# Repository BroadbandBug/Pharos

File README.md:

Pharos
======

APRS MSP430 Beacon

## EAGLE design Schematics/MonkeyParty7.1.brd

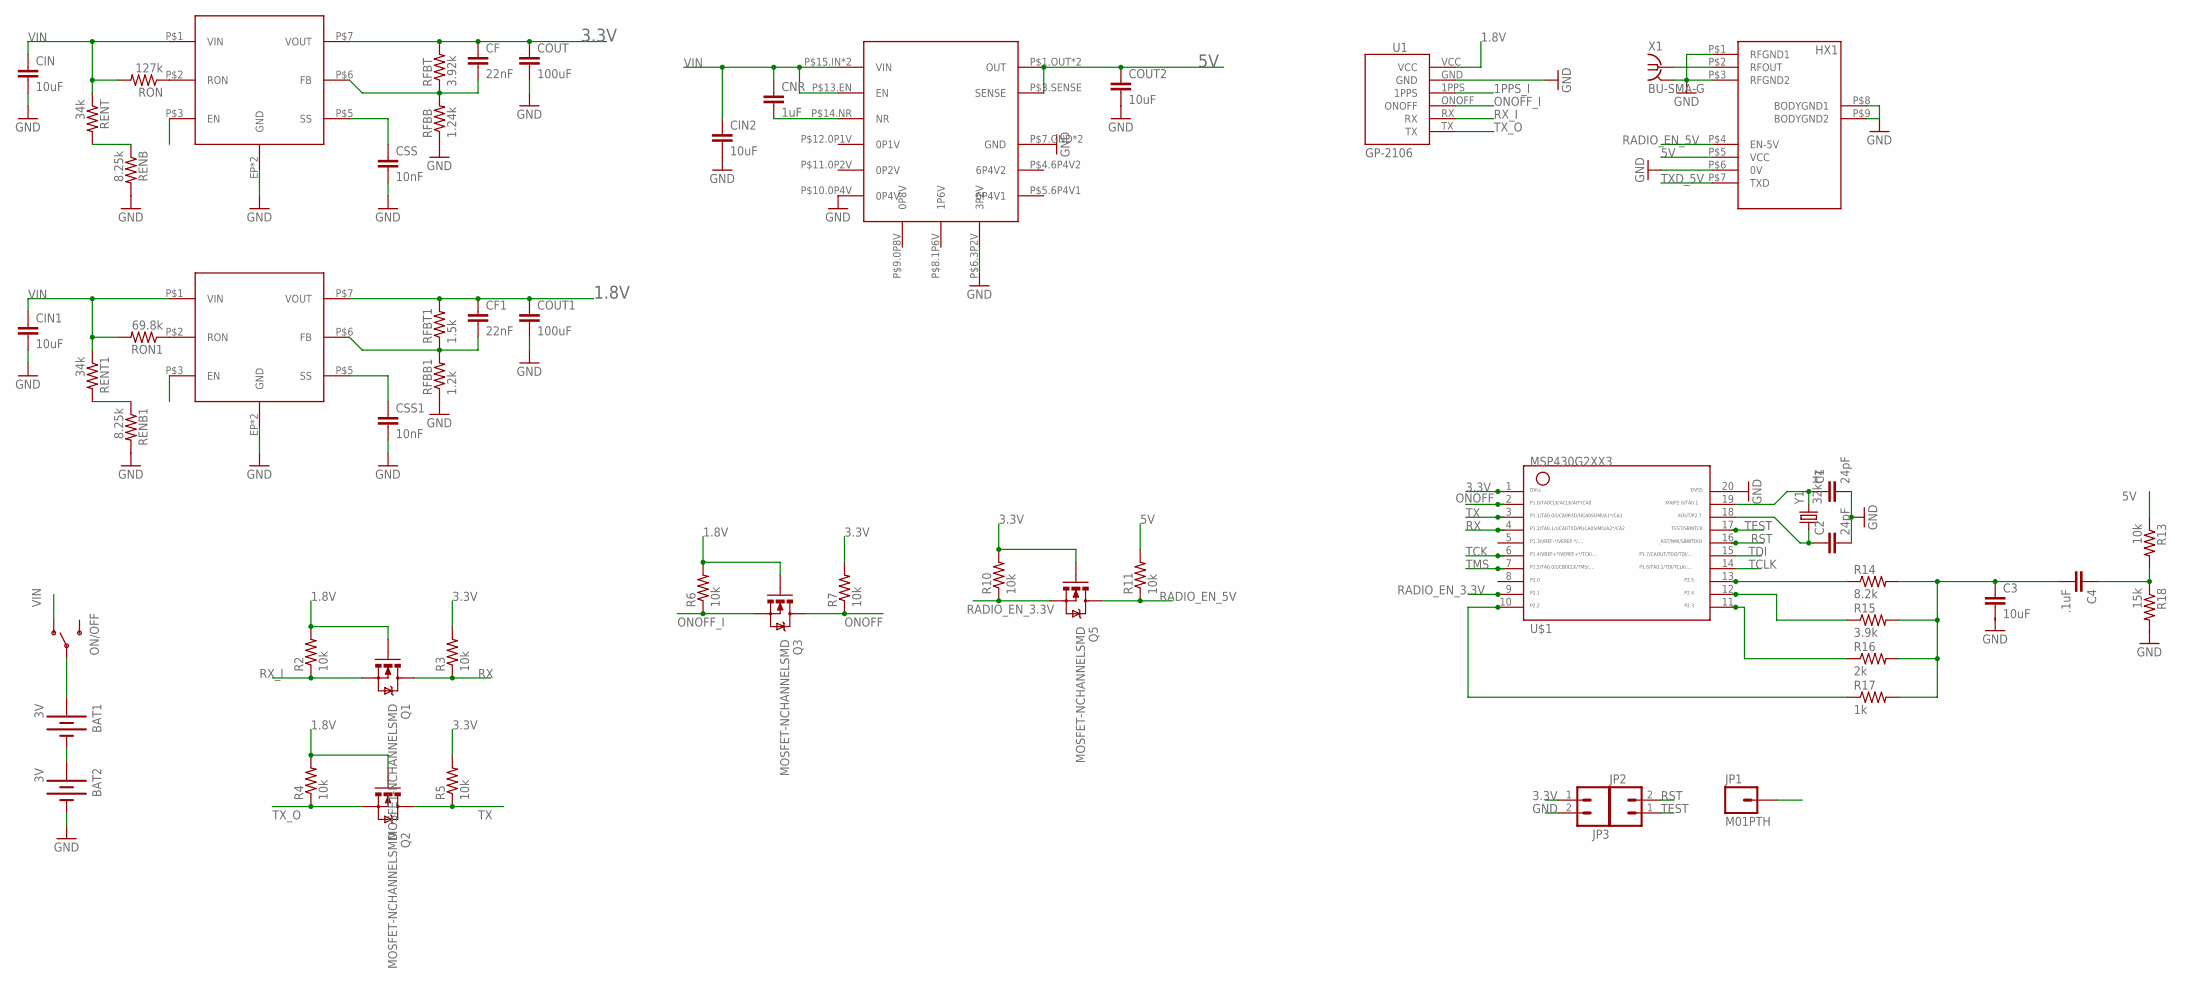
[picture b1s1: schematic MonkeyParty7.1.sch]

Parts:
1.8VREG, 3.3VREG: LMZ12001; TO-PMOD7PIN
5VREG: TPS7A4700; S-PVQFN-N20
BAT1, BAT2: 3V; BATTCON_245MM
C1, C2: 24pF; 1210
C3: 10uF; 0805
C4: .1uF; 0805
CF, CF1: 22nF; 0805
CIN, CIN1, CIN2: 10uF; 0805
CNR: 1uF; 0805
COUT, COUT1: 100uF; 1210
COUT2: 10uF; 0805
CSS, CSS1: 10nF; 1210
JP1: M01PTH; 1X01
JP2, JP3: M02PTH; 1X02
ON/OFF: SWITCH-SPSTKIT; SWITCH-SPDT_KIT
Q1, Q2, Q3, Q5: MOSFET-NCHANNELSMD; SOT23-3
R2, R3, R4, R5, R6, R7, R10, R11, R13: 10k; 0805
R14: 8.2k; 0805
R15: 3.9k; 0805
R16: 2k; 0805
R17: 1k; 0805
R18: 15k; 0805
RENB, RENB1: 8.25k; 0805
RENT, RENT1: 34k; 0805
RFBB: 1.24k; 0805
RFBB1: 1.2k; 0805
RFBT: 3.92k; 0805
RFBT1: 1.5k; 0805
RON: 127k; 0805
RON1: 69.8k; 0805
U1: GP-2106
U$1: G2XX3---PW20; PW20
U$2: HX1
X1: BU-SMA-G
Y1: 32kHz; CRYSTAL-32KHZ-SMD

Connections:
1.8V: 1.8VREG.P$7 (VOUT), CF1.1, COUT1.1, Q1.1 (G), Q2.1 (G), Q3.1 (G), R2.2, R4.2, R6.2, RFBT1.2, U1.VCC
1PPS_I: U1.1PPS
3.3V: 3.3VREG.P$7 (VOUT), CF.1, COUT.1, JP3.1, Q5.1 (G), R3.2, R5.2, R7.2, R10.2, RFBT.2, U$1.1
5V: 5VREG.P$1.OUT (OUT), 5VREG.P$3.SENSE (SENSE), 5VREG.P$20.OUT (OUT), COUT2.1, R11.2, R13.1, U$2.P$5 (VCC)
GND: 1.8VREG.EP (GND), 1.8VREG.P$4 (GND), 3.3VREG.EP (GND), 3.3VREG.P$4 (GND), 5VREG.P$6.3P2V (3P2V), 5VREG.P$7.GND (GND), 5VREG.P$10.0P4V (0P4V), 5VREG.P$21.GND (GND), BAT2.2 (-), C1.2, C2.2, CIN.2, CIN1.2, CIN2.2, COUT.2, COUT1.2, COUT2.2, CSS.2, CSS1.2, JP3.2, RENB.2, RENB1.2, RFBB.1, RFBB1.1, U1.GND, U$1.20, U$2.P$1 (RFGND1), U$2.P$3 (RFGND2), U$2.P$6 (0V), U$2.P$8 (BODYGND1), U$2.P$9 (BODYGND2), X1.2, X1.3 (2), X1.4 (2), X1.5 (2)
unnamed: 3.3VREG.P$2 (RON), RON.1
unnamed: U$2.P$2 (RFOUT), X1.1
unnamed: RENB.1, RENT.2
unnamed: BAT1.2 (-), BAT2.1 (+)
unnamed: 3.3VREG.P$5 (SS), CSS.1
unnamed: 3.3VREG.P$6 (FB), CF.2, RFBB.2, RFBT.1
unnamed: 1.8VREG.P$2 (RON), RON1.1
unnamed: BAT1.1 (+), ON/OFF.2
unnamed: RENB1.1, RENT1.2
unnamed: 1.8VREG.P$5 (SS), CSS1.1
unnamed: 1.8VREG.P$6 (FB), CF1.2, RFBB1.2, RFBT1.1
unnamed: 5VREG.P$14.NR (NR), CNR.2
unnamed: C1.1, U$1.19, Y1.X2 (2)
unnamed: C2.1, U$1.18, Y1.X1 (1)
unnamed: R14.1, U$1.13
unnamed: R15.1, U$1.12
unnamed: R16.1, U$1.11
unnamed: R17.1, U$1.10
ONOFF: Q3.3 (D), R7.1, U$1.2
ONOFF_I: Q3.2 (S), R6.1, U1.ONOFF
RADIO_EN_3.3V: Q5.2 (S), R10.1, U$1.9
RADIO_EN_5V: Q5.3 (D), R11.1, U$2.P$4 (EN-5V)
RST: JP2.2, U$1.16
RX: Q1.3 (D), R3.1, U$1.4
RX_I: Q1.2 (S), R2.1, U1.RX
TCK: U$1.6
TCLK: U$1.14
TDI: U$1.15
TEST: JP2.1, U$1.17
TMS: U$1.7
TX: Q2.3 (D), R5.1, U$1.3
TXD_3.3V: C3.1, C4.2, R14.2, R15.2, R16.2, R17.2
TXD_5V: C4.1, R13.2, R18.1, U$2.P$7 (TXD)
TX_O: Q2.2 (S), R4.1, U1.TX
VIN: 1.8VREG.P$1 (VIN), 1.8VREG.P$3 (EN), 3.3VREG.P$1 (VIN), 3.3VREG.P$3 (EN), 5VREG.P$13.EN (EN), 5VREG.P$15.IN (VIN), 5VREG.P$16.IN (VIN), CIN.1, CIN1.1, CIN2.1, CNR.1, JP1.1, ON/OFF.1 (O), RENT.1, RENT1.1, RON.2, RON1.2

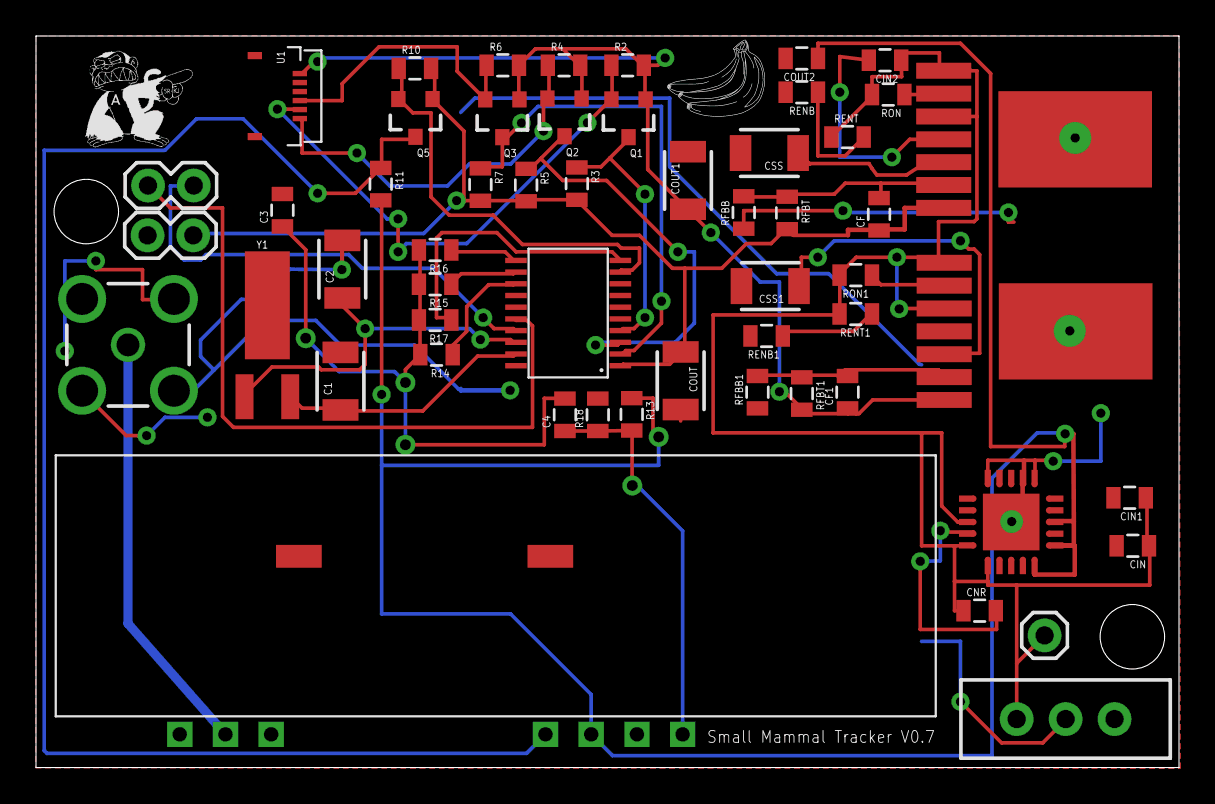
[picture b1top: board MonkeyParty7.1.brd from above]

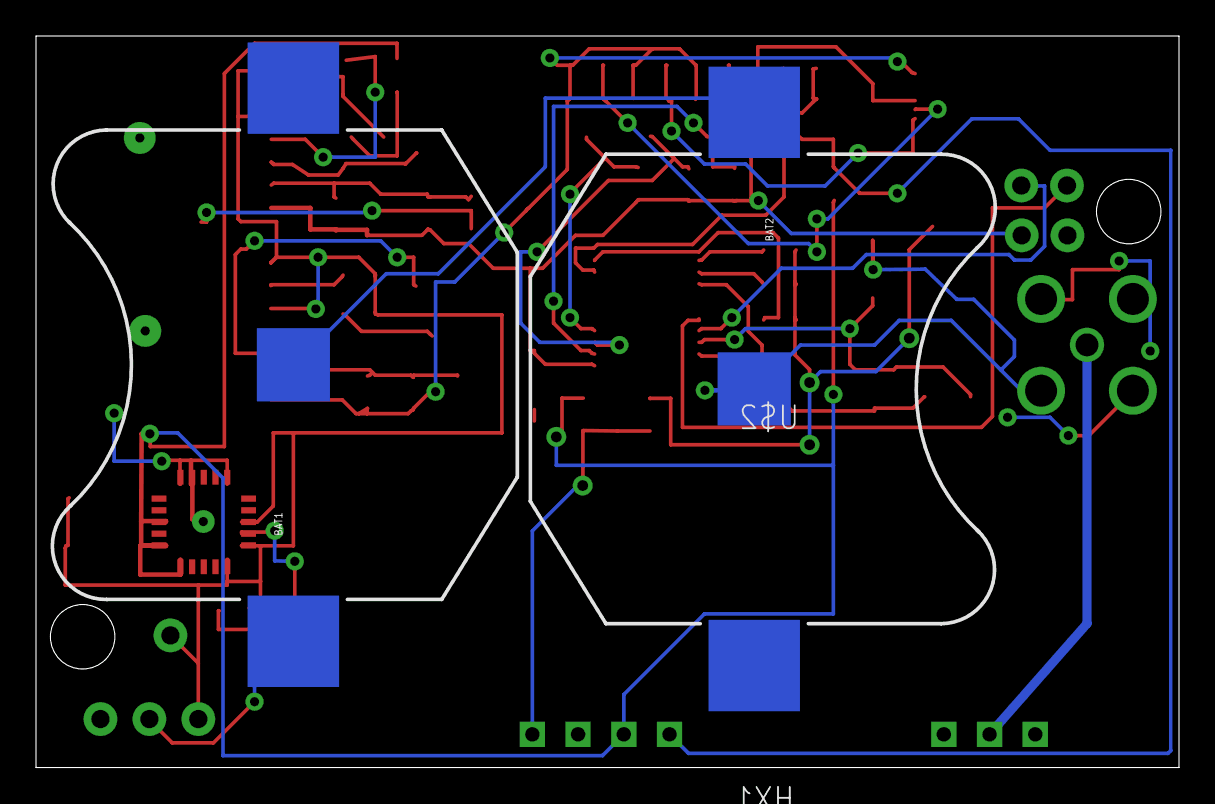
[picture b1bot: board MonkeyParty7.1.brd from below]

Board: 2 copper layers, 63.5 x 40.6 mm, 57 parts (2 on the bottom side), 35 nets.

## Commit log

2013-04-17 Initial upload from private dir
    Copied from "Final"
2013-04-18 Cleaning up file structure
2014-06-13 Added pictures of the final project

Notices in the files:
parts and their libraries:
SparkFun: Licensing: CC v3.0 Share-Alike You are welcome to use this library for commercial purposes.
